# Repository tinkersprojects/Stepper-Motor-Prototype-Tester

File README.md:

# Stepper-Motor-Prototype-Tester
[https://tinkersprojects.com/](https://tinkersprojects.com/)

This controller is made as a prototype tool to test mechanics from a stepper motor. On the controller, there is a button which is used to change the state of the motor. The controller can have 2 states set, one while the button is pressed ad one while the button is not pressed. The controller can be set using a serial user interface. There are 4 different states that can be set; stop, move to a position, move amount and continuously moving. Stop is stop to stop the motor. Move to a position is to move to a set position. Move amount is to move a set amount no matter what the other set state is. Continuously moving make the motor continuously move at a set speed in a direction.

2 different or the same state can be set, for example; state 1 (button = 0) is continuously moving and state 2 (button = 1) is Move to a position. This will make the motor continuously run but when the button is pressed, the motor will go to the set position. This means that the motor will return to the same spot even tho it has moved away at a random distance.
Another example would be setting the same state but with different speed setting or position settings.
To access the menu, plug the controller into the USB and the menu will appear in the serial console. This menu allows you to set how the controller reacts to the button press.
Welcome v1.0 Stepper motor controller

```
Commads:
    P – Program (ON Type, ON Distance, ON Speed, OFF Type, OFF Distance, OFF Speed)
    A – Move amount (Distance)
    T – Move To positon (Distance)
    S – Set setting (m1, m2, m3)
    D – Display details
    H – Help
Serial.println();
Type:
    0 – Stop
    1 – Move to position
    2 – Move amount
    3 – Continuously moving
```

The Arduino program and PCB is available from https://github.com/tinkersprojects/Stepper-Motor-Prototype-Tester
The PCB is available from https://tinkersprojects.com/product/stepper-motor-prototype-tester/

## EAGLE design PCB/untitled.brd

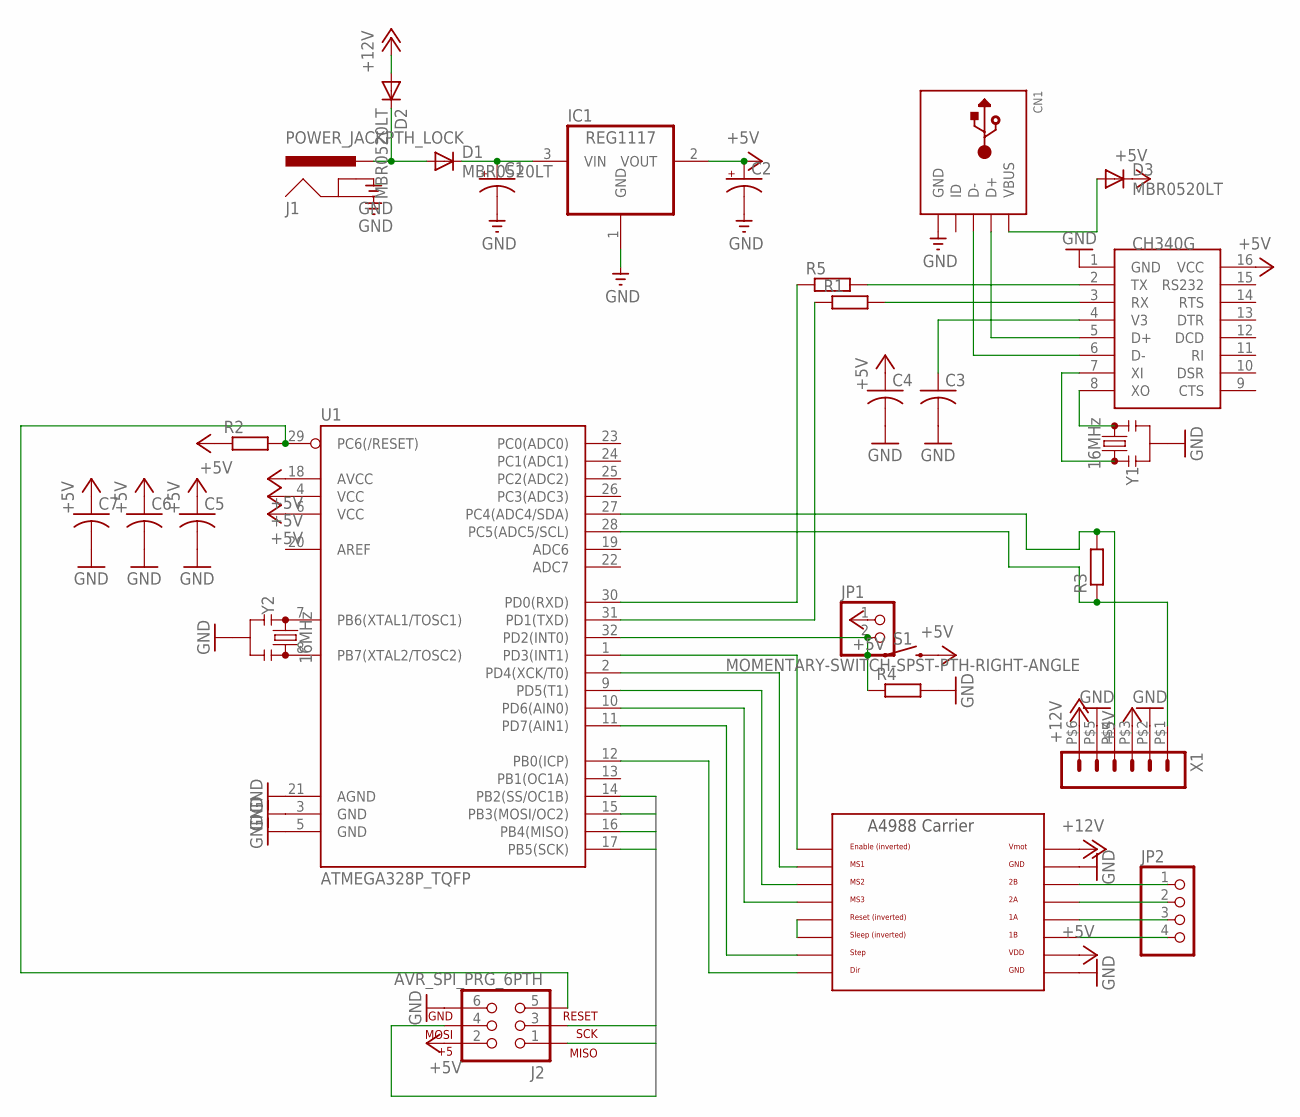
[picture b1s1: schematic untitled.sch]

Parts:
C1, C2: CPOL-US153CLV-0405; 153CLV-0405
C3, C4, C5, C6, C7: C-USC1210; C1210
CN1: USBMINIB; USB-MINIB
D1, D2, D3: MBR0520LT; SOD123
IC1: REG1117; SOT223
J1: POWER_JACKPTH_LOCK; POWER_JACK_PTH_LOCK
J2: AVR_SPI_PRG_6PTH; 2X3
JP1: PINHD-1X2; 1X02
JP2: PINHD-1X4; 1X04
R1, R2, R3, R4, R5: R-EU_MELF0207W; MINI_MELF-0207W
S1: MOMENTARY-SWITCH-SPST-PTH-RIGHT-ANGLE; TACTILE_SWITCH_PTH_RIGHT_ANGLE
U1: ATMEGA328P_TQFP; TQFP32-08
U$1: CH340G; SOIC16
U$2: A4988BREAKOUT
X1: HEADER_POS6_43045-0600; 43045-0600
Y1, Y2: 16MHz; RESONATOR-SMD-3.2X1.3

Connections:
+5V: C2.+, C4.1, C5.1, C6.1, C7.1, D3.C, IC1.2 (VOUT), J2.2, JP1.1, R2.1, S1.2, U1.4 (VCC), U1.6 (VCC), U1.18 (AVCC), U$1.16 (VCC), U$2.VDD, X1.P$3 (3)
+12V: D2.A, U$2.VMOT, X1.P$6 (6)
CAN_CS: U1.14 (PB2(SS/OC1B))
GND: C1.-, C2.-, C3.2, C4.2, C5.2, C6.2, C7.2, CN1.GND, IC1.1 (GND), J1.GND, J1.GNDBREAK, J2.6, R4.2, U1.3 (GND), U1.5 (GND), U1.21 (AGND), U$1.1 (GND), U$2.GND, U$2.GND@0 (GND), X1.P$2 (2), X1.P$5 (5), Y1.2, Y2.2
MISO: J2.1, U1.16 (PB4(MISO))
MOSI: J2.4, U1.15 (PB3(MOSI/OC2))
unnamed: D1.A, D2.C, J1.PWR
unnamed: R1.2, U$1.3 (RX)
unnamed: U1.1 (PD3(INT1)), U$2.EN
unnamed: U1.2 (PD4(XCK/T0)), U$2.MS1
unnamed: U1.8 (PB7(XTAL2/TOSC2)), Y2.3
unnamed: U1.7 (PB6(XTAL1/TOSC1)), Y2.1
unnamed: J2.5, R2.2, U1.29 (PC6(/RESET))
unnamed: R3.2, U1.27 (PC4(ADC4/SDA)), X1.P$4 (4)
unnamed: U1.9 (PD5(T1)), U$2.MS2
unnamed: U1.10 (PD6(AIN0)), U$2.MS3
unnamed: R3.1, U1.28 (PC5(ADC5/SCL)), X1.P$1 (1)
unnamed: C1.+, D1.C, IC1.3 (VIN)
unnamed: JP1.2, R4.1, S1.1, U1.32 (PD2(INT0))
unnamed: U1.11 (PD7(AIN1)), U$2.STEP
unnamed: U1.12 (PB0(ICP)), U$2.DIR
unnamed: U$2.RST, U$2.SLP (SLEEP)
unnamed: JP2.1, U$2.2B
unnamed: JP2.2, U$2.2A
unnamed: JP2.3, U$2.1A
unnamed: JP2.4, U$2.1B
unnamed: U$1.8 (XO), Y1.3
unnamed: U$1.7 (XI), Y1.1
unnamed: R5.1, U1.30 (PD0(RXD))
unnamed: R1.1, U1.31 (PD1(TXD))
unnamed: R5.2, U$1.2 (TX)
unnamed: CN1.D+, U$1.5 (D+)
unnamed: CN1.D-, U$1.6 (D-)
unnamed: CN1.VBUS, D3.A
unnamed: C3.1, U$1.4 (V3)
SCK: J2.3, U1.17 (PB5(SCK))

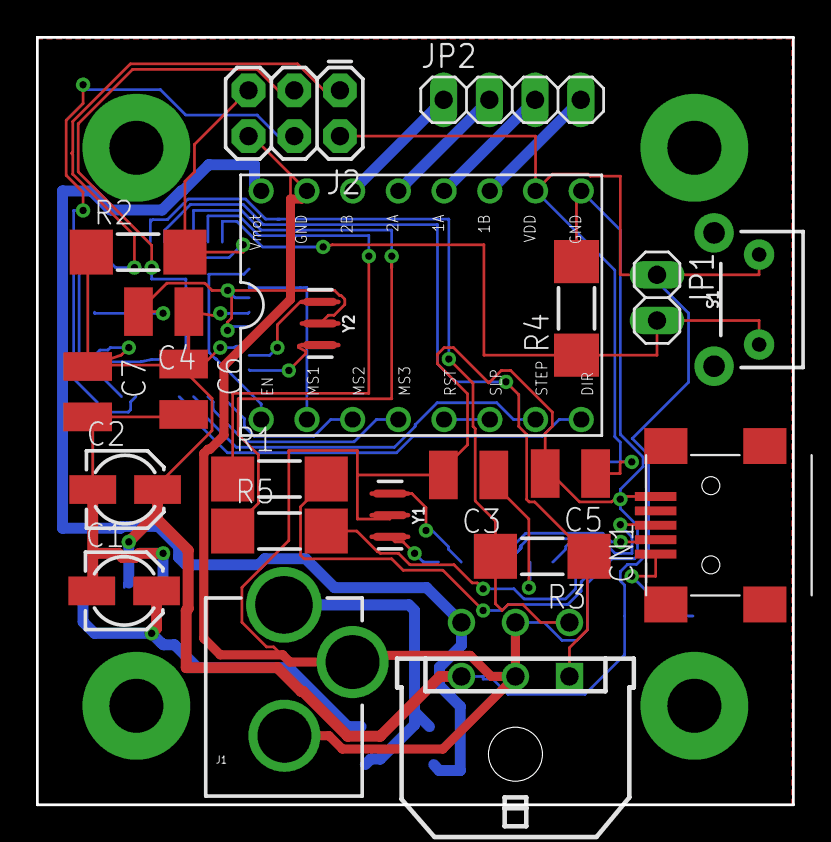
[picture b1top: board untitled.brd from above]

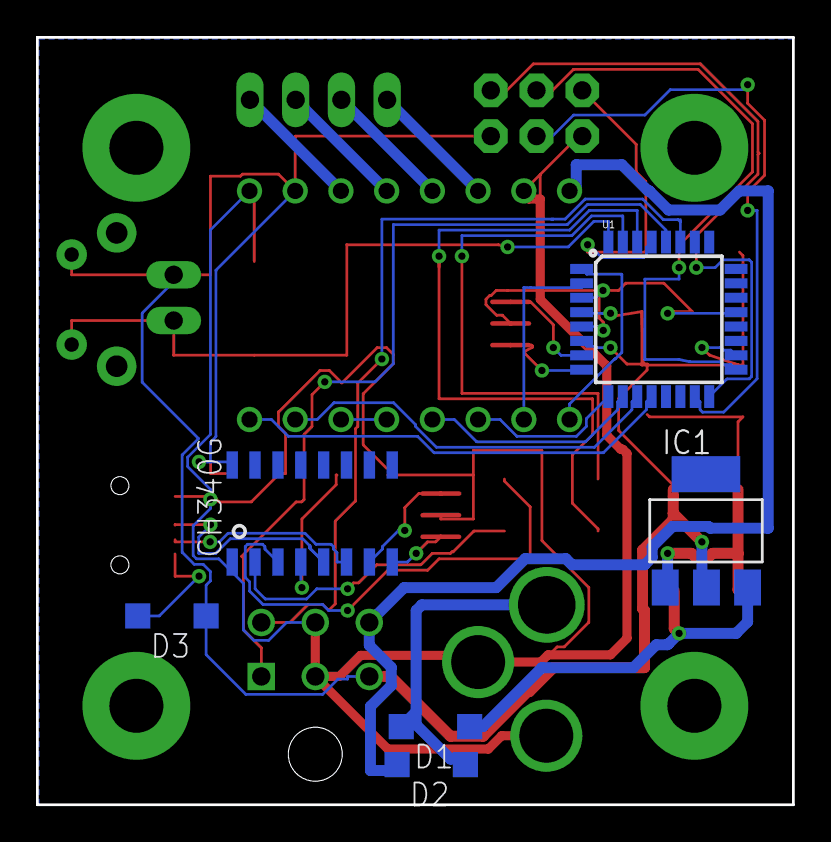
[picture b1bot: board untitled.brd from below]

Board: 2 copper layers, 42.0 x 42.6 mm, 28 parts (6 on the bottom side), 35 nets.

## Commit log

2018-04-12 Add files via upload
    upload Arduino files
2018-04-12 Add files via upload
    upload PCB files

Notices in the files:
parts and their libraries:
SparkFun-DigitalIC: Licensing: Creative Commons ShareAlike 4.0 International - https://creativecommons.org/licenses/by-sa/4.0
supply0: Copyright (C) 2007, Bob Starr
